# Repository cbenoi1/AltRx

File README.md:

# AltRx

Kicad 7.x projects

https://github.com/cbenoi1/AltRx/blob/main/maac_rx.png

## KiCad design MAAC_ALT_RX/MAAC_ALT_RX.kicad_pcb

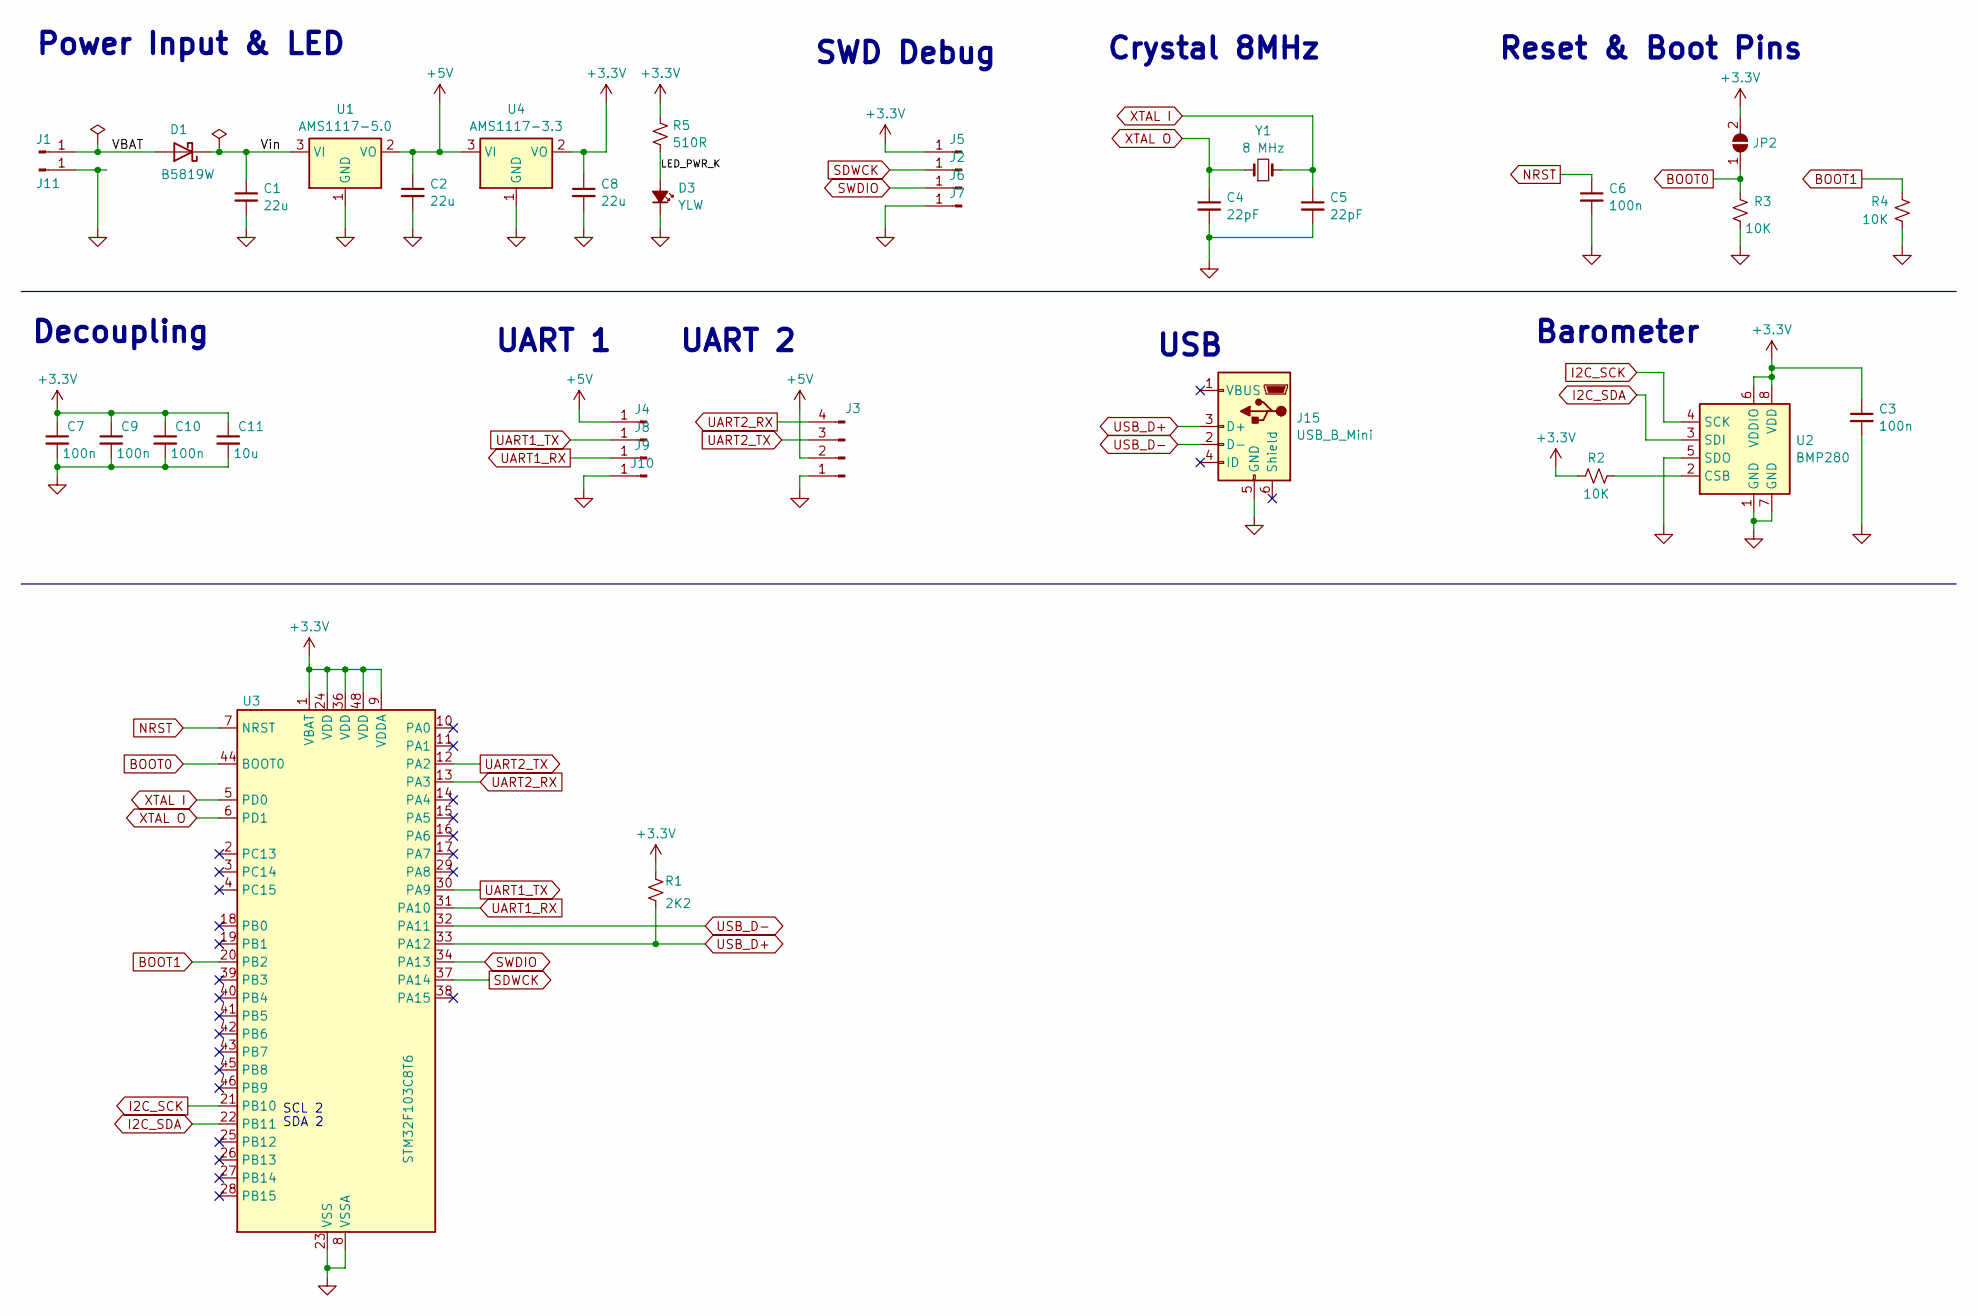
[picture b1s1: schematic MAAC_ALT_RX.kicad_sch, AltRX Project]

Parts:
C1, C2, C8: 22u; C_0805_2012Metric; LCSC C45783
C3, C6, C7, C9, C10: 100n; C_0603_1608Metric; LCSC C14663
C4, C5: 22pF; C_0402_1005Metric; LCSC C1555
C11: 10u; C_1210_3225Metric; LCSC C13585
D1: B5819W; D_SOD-123; LCSC C8598
D3: YLW; LED_0603_1608Metric; LCSC C2286
J1, J11: Conn_01x01_Pin; TestPoint_Pad_4.0x4.0mm
J2, J4, J5, J6, J7, J8, J9, J10: Conn_01x01_Pin; TestPoint_Pad_1.0x1.0mm
J3: Conn_01x04_Pin; PinSocket_1x04_P2.54mm_Vertical
J15: USB_B_Mini; USB_Micro-B_Wuerth_629105150521
JP2: SolderJumper_2_Open; SolderJumper-2_P1.3mm_Open_RoundedPad1.0x1.5mm
R1: 2K2; R_0402_1005Metric; LCSC C25879
R2, R3, R4: 10K; R_0402_1005Metric; LCSC C25744
R5: 510R; R_0402_1005Metric; LCSC C25123
U1: AMS1117-5.0; SOT-223; LCSC C6187
U2: BMP280; Bosch_LGA-8_2x2.5mm_P0.65mm_ClockwisePinNumbering; LCSC C83291
U3: STM32F103C8T6; LQFP-48_7x7mm_P0.5mm; LCSC C8734
U4: AMS1117-3.3; SOT-223; LCSC C6186
Y1: 8 MHz; Crystal_SMD_5032-2Pin_5.0x3.2mm; LCSC C115962

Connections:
+3.3V: C3.1, C7.1, C8.1, C9.1, C10.1, C11.1, J5.1, JP2.2 (B), R1.1, R2.1, R5.1, U2.6 (VDDIO), U2.8 (VDD), U3.1 (VBAT), U3.9 (VDDA), U3.24 (VDD), U3.36 (VDD), U3.48 (VDD), U4.2 (VO)
+5V: C2.1, J3.2, J4.1, U1.2 (VO), U4.3 (VI)
/LED_PWR_K: D3.2 (A), R5.2
/VBAT: D1.2 (A), J1.1
/Vin: C1.1, D1.1 (K), U1.3 (VI)
BOOT0: JP2.1 (A), R3.2, U3.44 (BOOT0)
BOOT1: R4.2, U3.20 (PB2)
GND: C1.2, C2.2, C3.2, C4.2, C5.2, C6.2, C7.2, C8.2, C9.2, C10.2, C11.2, D3.1 (K), J3.1, J7.1, J10.1, J11.1, J15.5 (GND), R3.1, R4.1, U1.1 (GND), U2.1 (GND), U2.5 (SDO), U2.7 (GND), U3.8 (VSSA), U3.23 (VSS), U3.35 (VSS), U3.47 (VSS), U4.1 (GND)
I2C_SCK: U2.4 (SCK), U3.21 (PB10)
I2C_SDA: U2.3 (SDI), U3.22 (PB11)
NRST: C6.1, U3.7 (NRST)
unnamed: R2.2, U2.2 (CSB)
SDWCK: J2.1, U3.37 (PA14)
SWDIO: J6.1, U3.34 (PA13)
UART1_RX: J9.1, U3.31 (PA10)
UART1_TX: J8.1, U3.30 (PA9)
UART2_RX: J3.4, U3.13 (PA3)
UART2_TX: J3.3, U3.12 (PA2)
USB_D+: J15.3 (D+), R1.2, U3.33 (PA12)
USB_D-: J15.2 (D-), U3.32 (PA11)
XTAL I: C5.1, U3.5 (PD0), Y1.2
XTAL O: C4.1, U3.6 (PD1), Y1.1

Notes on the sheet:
Decoupling
SDA 2
SWD Debug
Barometer
Reset & Boot Pins
SCL 2
Crystal 8MHz
UART 1
Power Input & LED
USB
UART 2

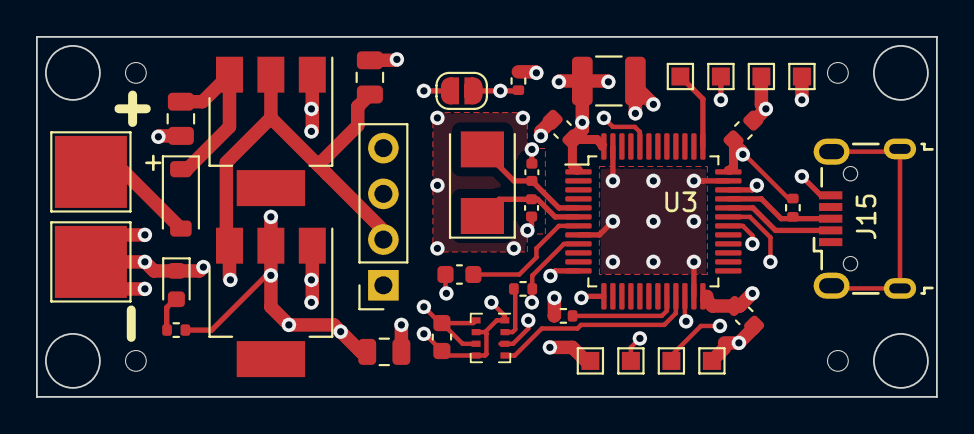
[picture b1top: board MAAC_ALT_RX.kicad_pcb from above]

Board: 4 copper layers, 50.0 x 20.0 mm, 36 parts (0 on the bottom side), 22 nets.

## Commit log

2023-08-02 AltRX v1.0
    initial version

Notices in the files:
MAAC_ALT_RX/MAAC_ALT_RX.kicad_pcb:
(c) 2023 Claude BENOIT
